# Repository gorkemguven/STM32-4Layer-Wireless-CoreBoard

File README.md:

# STM32 4-Layer Wireless Core Board

A compact, 4-layer reusable STM32 wireless core board designed in KiCad. It functions both as a standalone USB-to-Wireless dongle/sniffer and as a modular core block for integration into larger IoT and embedded carrier boards.

---

## 📌 Board Overview

| 3D / Top Layer View | Inner Ground Plane |
| :---: | :---: |
|  |  |

---

## 🚀 Key Features

* **MCU & Core:** STM32 microcontroller with integrated RF capabilities.
* **4-Layer Optimized Stackup:**
  * **Layer 1 (Top):** High-speed signals, RF trace, and localized GND polygon.
  * **Layer 2 (Inner 1):** Solid, unbroken Ground Reference Plane for signal integrity and RF return paths.
  * **Layer 3 (Inner 2):** Dedicated power plane split (3.3V and VBUS) optimized with Non-Functional Pad (NFP) removal to maximize copper pouring.
  * **Layer 4 (Bottom):** Auxiliary low-speed signal routing (UART TX/RX) and continuous GND shielding.
* **RF Architecture:**
  * 50 Ω impedance-matched microstrip line leading to antenna pad.
  * Perimeter and coplanar ground via stitching for minimal EMI and optimal shield performance.
* **Power Management:**
  * USB Type-C input with CC1/CC2 pull-down configuration.
  * Electrostatic Discharge (ESD) protection IC (`USBLC6-2SC6`) on differential USB data lines.
  * Low-noise, low-dropout linear regulator (`AP2112K-3.3V`, up to 600 mA).
* **Interfaces & Debugging:**
  * Dedicated Serial Wire Debug (SWD) test pad group for programming and hardware breakpoints.
  * Hardware `NRST` and `BOOT0` selection pads.
  * UART interface (`LOCAL_TX` / `LOCAL_RX`) with 220 Ω series current-limiting resistors for real-time logging.

---

## 📐 Schematic Sheets

| Sheet 1: MCU & RF Core | Sheet 2: Type-C & LDO Power |
| :---: | :---: |
|  |  |

---

## 🗂️ Layer Stackup Details

| Layer 1: Top Signal / GND | Layer 2: Inner Full GND |
| :---: | :---: |
|  |  |

| Layer 3: Inner Power (VBUS & 3.3V) | Layer 4: Bottom Signal / GND |
| :---: | :---: |
|  |  |

---

## 📦 Manufacturing & Assembly Files

All fabrication and assembly files are pre-generated and ready for fabrication (JLCPCB, PCBWay, etc.):

* **Gerber & Drill Package:** [`STM-32_Gerber.zip`](STM-32_Gerber.zip)
* **Bill of Materials (BOM):** [`bom.csv`](bom.csv)
* **Component Placement (CPL / Centroid):** [`positions.csv`](positions.csv)
* **Designators:** [`designators.csv`](designators.csv)
* **Netlist IPC:** [`netlist.ipc`](netlist.ipc)

---

## 💻 Hardware Design Files

To open and modify the native project, open `STM-32.kicad_pro` using KiCad.

* `STM-32.kicad_pro`: KiCad project settings file
* `STM-32.kicad_sch`: Root schematic sheet
* `TYPE-C and LDO.kicad_sch`: Sub-sheet for power distribution
* `STM-32.kicad_pcb`: 4-layer PCB layout

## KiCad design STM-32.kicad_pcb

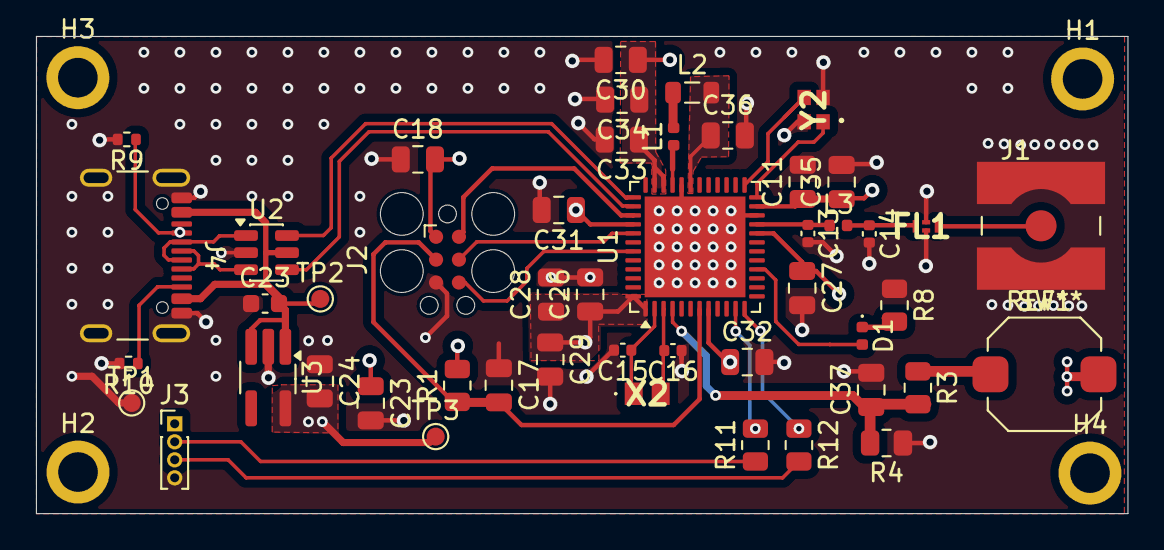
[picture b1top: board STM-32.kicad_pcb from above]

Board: 4 copper layers, 60.6 x 26.5 mm, 52 parts (0 on the bottom side), 31 nets.

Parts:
C11: 100pF; C_0805_2012Metric
C13: 0.8pF; C_0402_1005Metric
C14: 0.3pF; C_0402_1005Metric
C15, C16: 15pF; C_0402_1005Metric
C17, C18, C23, C26, C27, C28, C30, C31, C32, C33, C35, C37: 100nF; C_0805_2012Metric
C23#2: 4.7uF; C_0603_1608Metric
C24: 4.7; C_0805_2012Metric
C29, C34, C36: 4.7uF; C_0805_2012Metric
D1: LED; LED_0402_1005Metric
FL1: Low_Pass_Filter; DLF162500LT5028A1
H1, H2, H3, H4: MountingHole; MountingHole_2.2mm_M2_ISO7380_Pad
J1: Antenna; SMA_Wurth_60312102114405_Vertical
J2: TC2030; Tag-Connect_TC2030-IDC-FP_2x03_P1.27mm_Vertical
J3: Conn_01x04_Pin; PinHeader_1x04_P1.00mm_Vertical
J4: USB_C_Receptacle_USB2.0_16P; USB_C_Receptacle_GCT_USB4105-xx-A_16P_TopMnt_Horizontal
L1: 10nH; L_0402_1005Metric
L2: 10uH; L_0805_2012Metric
L3: 2.7nH; L_0402_1005Metric
R1, R4: 10k; R_0805_2012Metric
R3: 470; R_0805_2012Metric
R8, R11, R12: 220; R_0805_2012Metric
R9, R10: 5.1k; R_0402_1005Metric
SW1: SW_Push; SW_Push_1TS009xxxx-xxxx-xxxx_6x6x5mm
TP1, TP2, TP3: TestPoint; TestPoint_Pad_D1.0mm
U1: STM32WB55CEU6; QFN-48-1EP_7x7mm_P0.5mm_EP5.6x5.6mm
U2: USBLC6-2SC6; SOT-23-6
U3: AP2112K-3.3; TSOT-23-5_HandSoldering
X2: 32.768kHz; NX2012SA32768KHZEXS00AMU00797
Y2: 32MGHz; NX2016SA32MHZEXS00ACS06654

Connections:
3.3V: C11.1, C18.2, C23.1, C24.2, C26.1, C27.1, C28.1, C29.1, C30.1, C31.1, C32.1, C33.1, C34.1, C35.1, J2.1 (VCC), J3.1, R1.2, SW1.2, TP3.1 (1_1), U1.1 (VBAT), U1.8 (VDDA), U1.20 (VDD), U1.23 (VDDRF), U1.34 (VDDSMPS), U1.35 (VDD), U1.40 (VDDUSB), U1.48 (VDD), U3.5 (VOUT)
/LOCAL_RX: J3.3, R12.2
/LOCAL_TX: J3.2, R11.1
/UART_RX: R12.1, U1.12 (PA3)
/UART_TX: R11.2, U1.11 (PA2)
BOOT0: C37.1, R3.2, R4.2, U1.4 (PH3)
D+: J4.A6 (D+), J4.B6 (D+), U2.3 (I/O2)
D-: J4.A7 (D-), J4.B7 (D-), U2.1 (I/O1)
GNDD: C11.2, C13.2, C14.2, C15.2, C16.1, C17.1, C18.1, C23.2, C23#2.1, C24.1, C26.2, C27.2, C28.2, C29.2, C30.2, C31.2, C32.2, C33.2, C34.2, C35.2, C36.2, C37.2, FL1.2 (GND_1), FL1.4 (GND_2), J1.2 (Ext), J2.5 (GND), J3.4, J4.A1 (GND), J4.A12 (GND), J4.B1 (GND), J4.B12 (GND), J4.SH (SHIELD), R4.1, R8.1, R9.2, R10.2, TP1.1 (1_1), U1.22 (VSSRF), U1.32 (VSSSMPS), U1.49 (VSS), U2.2 (GND), U3.2 (GND), Y2.2 (3), Y2.4 (2)
LSE_IN: C15.1, U1.2 (PC14), X2.1 (CRYSTAL_2)
LSE_OUT: C16.2, U1.3 (PC15), X2.2 (CRYSTAL_2)
unnamed: D1.2 (A), U1.16 (PA7)
unnamed: D1.1 (K), R8.2
unnamed: J4.A5 (CC1), R9.1
unnamed: J4.B5 (CC2), R10.1
unnamed: R3.1, SW1.1
OSC_IN: U1.25 (OSC_IN), Y2.3 (1)
OSC_OUT: U1.24 (OSC_OUT), Y2.1 (4)
RF: C13.1, L3.1, U1.21 (RF1)
RF_ANT: FL1.3 (OUT), J1.1 (In)
RF_Match: C14.1, FL1.1 (IN), L3.2
SMPSFB: C36.1, L2.2, U1.31 (VFBSMPS)
SMPSLX: L1.1, U1.33 (VLXSMPS)
SMPSLXL: L1.2, L2.1
SWD_CLK: J2.4 (SWCLK), U1.41 (PA14)
SWD_DIO: J2.2 (SWDIO), U1.39 (PA13)
SWD_NRST: C17.2, J2.3 (~RESET), R1.1, U1.7 (NRST)
SWD_TRC: J2.6 (SWO), U1.43 (PB3)
USB_D+: U1.38 (PA12), U2.4 (I/O2)
USB_D-: U1.37 (PA11), U2.6 (I/O1)
VBUS: C23#2.2, J4.A4 (VBUS), J4.A9 (VBUS), J4.B4 (VBUS), J4.B9 (VBUS), TP2.1 (1_1), U2.5 (VBUS), U3.1 (VIN), U3.3 (EN)

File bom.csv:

Designator,Footprint,Quantity,Value,LCSC Part #
C11,0805,1,100pF,
C13,0402,1,0.8pF,
C14,0402,1,0.3pF,
"C15, C16",0402,2,15pF,
"C17, C18, C23_2, C26, C27, C28, C30, C31, C32, C33, C35, C37",0805,12,100nF,
C23,0603,1,4.7uF,
C24,0805,1,4.7,
"C29, C34, C36",0805,3,4.7uF,
D1,0402,1,LED,
FL1,DLF162500LT5028A1,1,Low_Pass_Filter,
J1,SMA_Wurth_60312102114405_Vertical,1,Antenna,
J3,PinHeader_1x04_P1.00mm_Vertical,1,Conn_01x04_Pin,
J4,USB_C_Receptacle_GCT_USB4105-xx-A_16P_TopMnt_Horizontal,1,USB_C_Receptacle_USB2.0_16P,
L1,0402,1,10nH,
L2,0805,1,10uH,
L3,0402,1,2.7nH,
"R1, R4",0805,2,10k,
"R10, R9",0402,2,5.1k,
"R11, R12, R8",0805,3,220,
R3,0805,1,470,
SW1,SW_Push_1TS009xxxx-xxxx-xxxx_6x6x5mm,1,SW_Push,
"TP1, TP2, TP3",TestPoint_Pad_D1.0mm,3,TestPoint,
U1,QFN-48-1EP_7x7mm_P0.5mm_EP5.6x5.6mm,1,STM32WB55CEU6,
U2,SOT-23-6,1,USBLC6-2SC6,
U3,TSOT-23-5_HandSoldering,1,AP2112K-3.3,
X2,NX2012SA32768KHZEXS00AMU00797,1,32.768kHz,
Y2,NX2016SA32MHZEXS00ACS06654,1,32MGHz,
